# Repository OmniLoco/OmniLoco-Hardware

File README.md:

OmniLoco Hardware
=================

The official repository for all of the hardware used by and created for the OmniLoco
project.

Repository Contents
-------------------

### Top Level

* OmniRotor -- Sources for the OmniRotor platform, a sophisticated autonomous aircraft controller.
* Library -- Script files for individual EAGLE packages, symbols and devices. See below for more
information.

### Tools

* OmniRotor_PogoPlate -- Used for the automated programming and testing of production OmniRotor devices.

EAGLE Library
-------------
The EAGLE library used for the OmniLoco project has been split up into individual package,
symbol and device script files. This is done so git can track the changes of each individual
part of the library, rather than simply tracking one monolithic binary file.

Exporting the library must be done before every commit which which includes changes to the
library. This process could be automated, although it's much easier to do it by hand for now.

### Building the library from this repo
1. Open a new library (or open an existing OmniLoco library)
2. Run the lbrbuild.ulp script (located in the `Library` directory)
3. Point to the generated (or downloaded from git) `librarydefaults.scr` when prompted
4. All the packages/devices/symbols are added to the new/existing library

### Exporting the library after making changes
If you are on Windows and using EAGLE 6.3.0 you can use the `Library/_dump_library.bat` script

1. Open the OmniLoco library
2. File > Export > Script (This will generate one large script with all the devices in it)
3. Save it to the `Library` directory as `_full_library.scr`
4. Run the lbrdump.ulp script (located in the `Library` directory)
5. Open the exported library file (`_full_library.scr` from step 3)

The method for exporting and building an EAGLE library using script files is adapted from 
[DangerousPrototypes][1].

Contributing
------------

1. Fork it.
2. Create a branch (`git checkout -b my_hardware`)
3. Commit your changes (`git commit -am "Added Awesome Changes"`)
4. Push to the branch (`git push origin my_hardware`)
5. Create an issue with a link to your branch, or submit a pull request
6. Enjoy a refreshing beverage and wait

License
-------
All OmniLoco hardware is open source and compliant with the [Open Source Hardware Definition][2].

Copyright (c) 2012 by the OmniLoco Foundation. This work is made available under the terms of the Creative Commons Attribution-ShareAlike 3.0 license, http://creativecommons.org/licenses/by-sa/3.0/.

[1]: http://dangerousprototypes.com/docs/Dangerous_Prototypes_Cadsoft_Eagle_parts_library
[2]: http://freedomdefined.org/OSHW#Open_Source_Hardware_.28OSHW.29_Definition_1.0

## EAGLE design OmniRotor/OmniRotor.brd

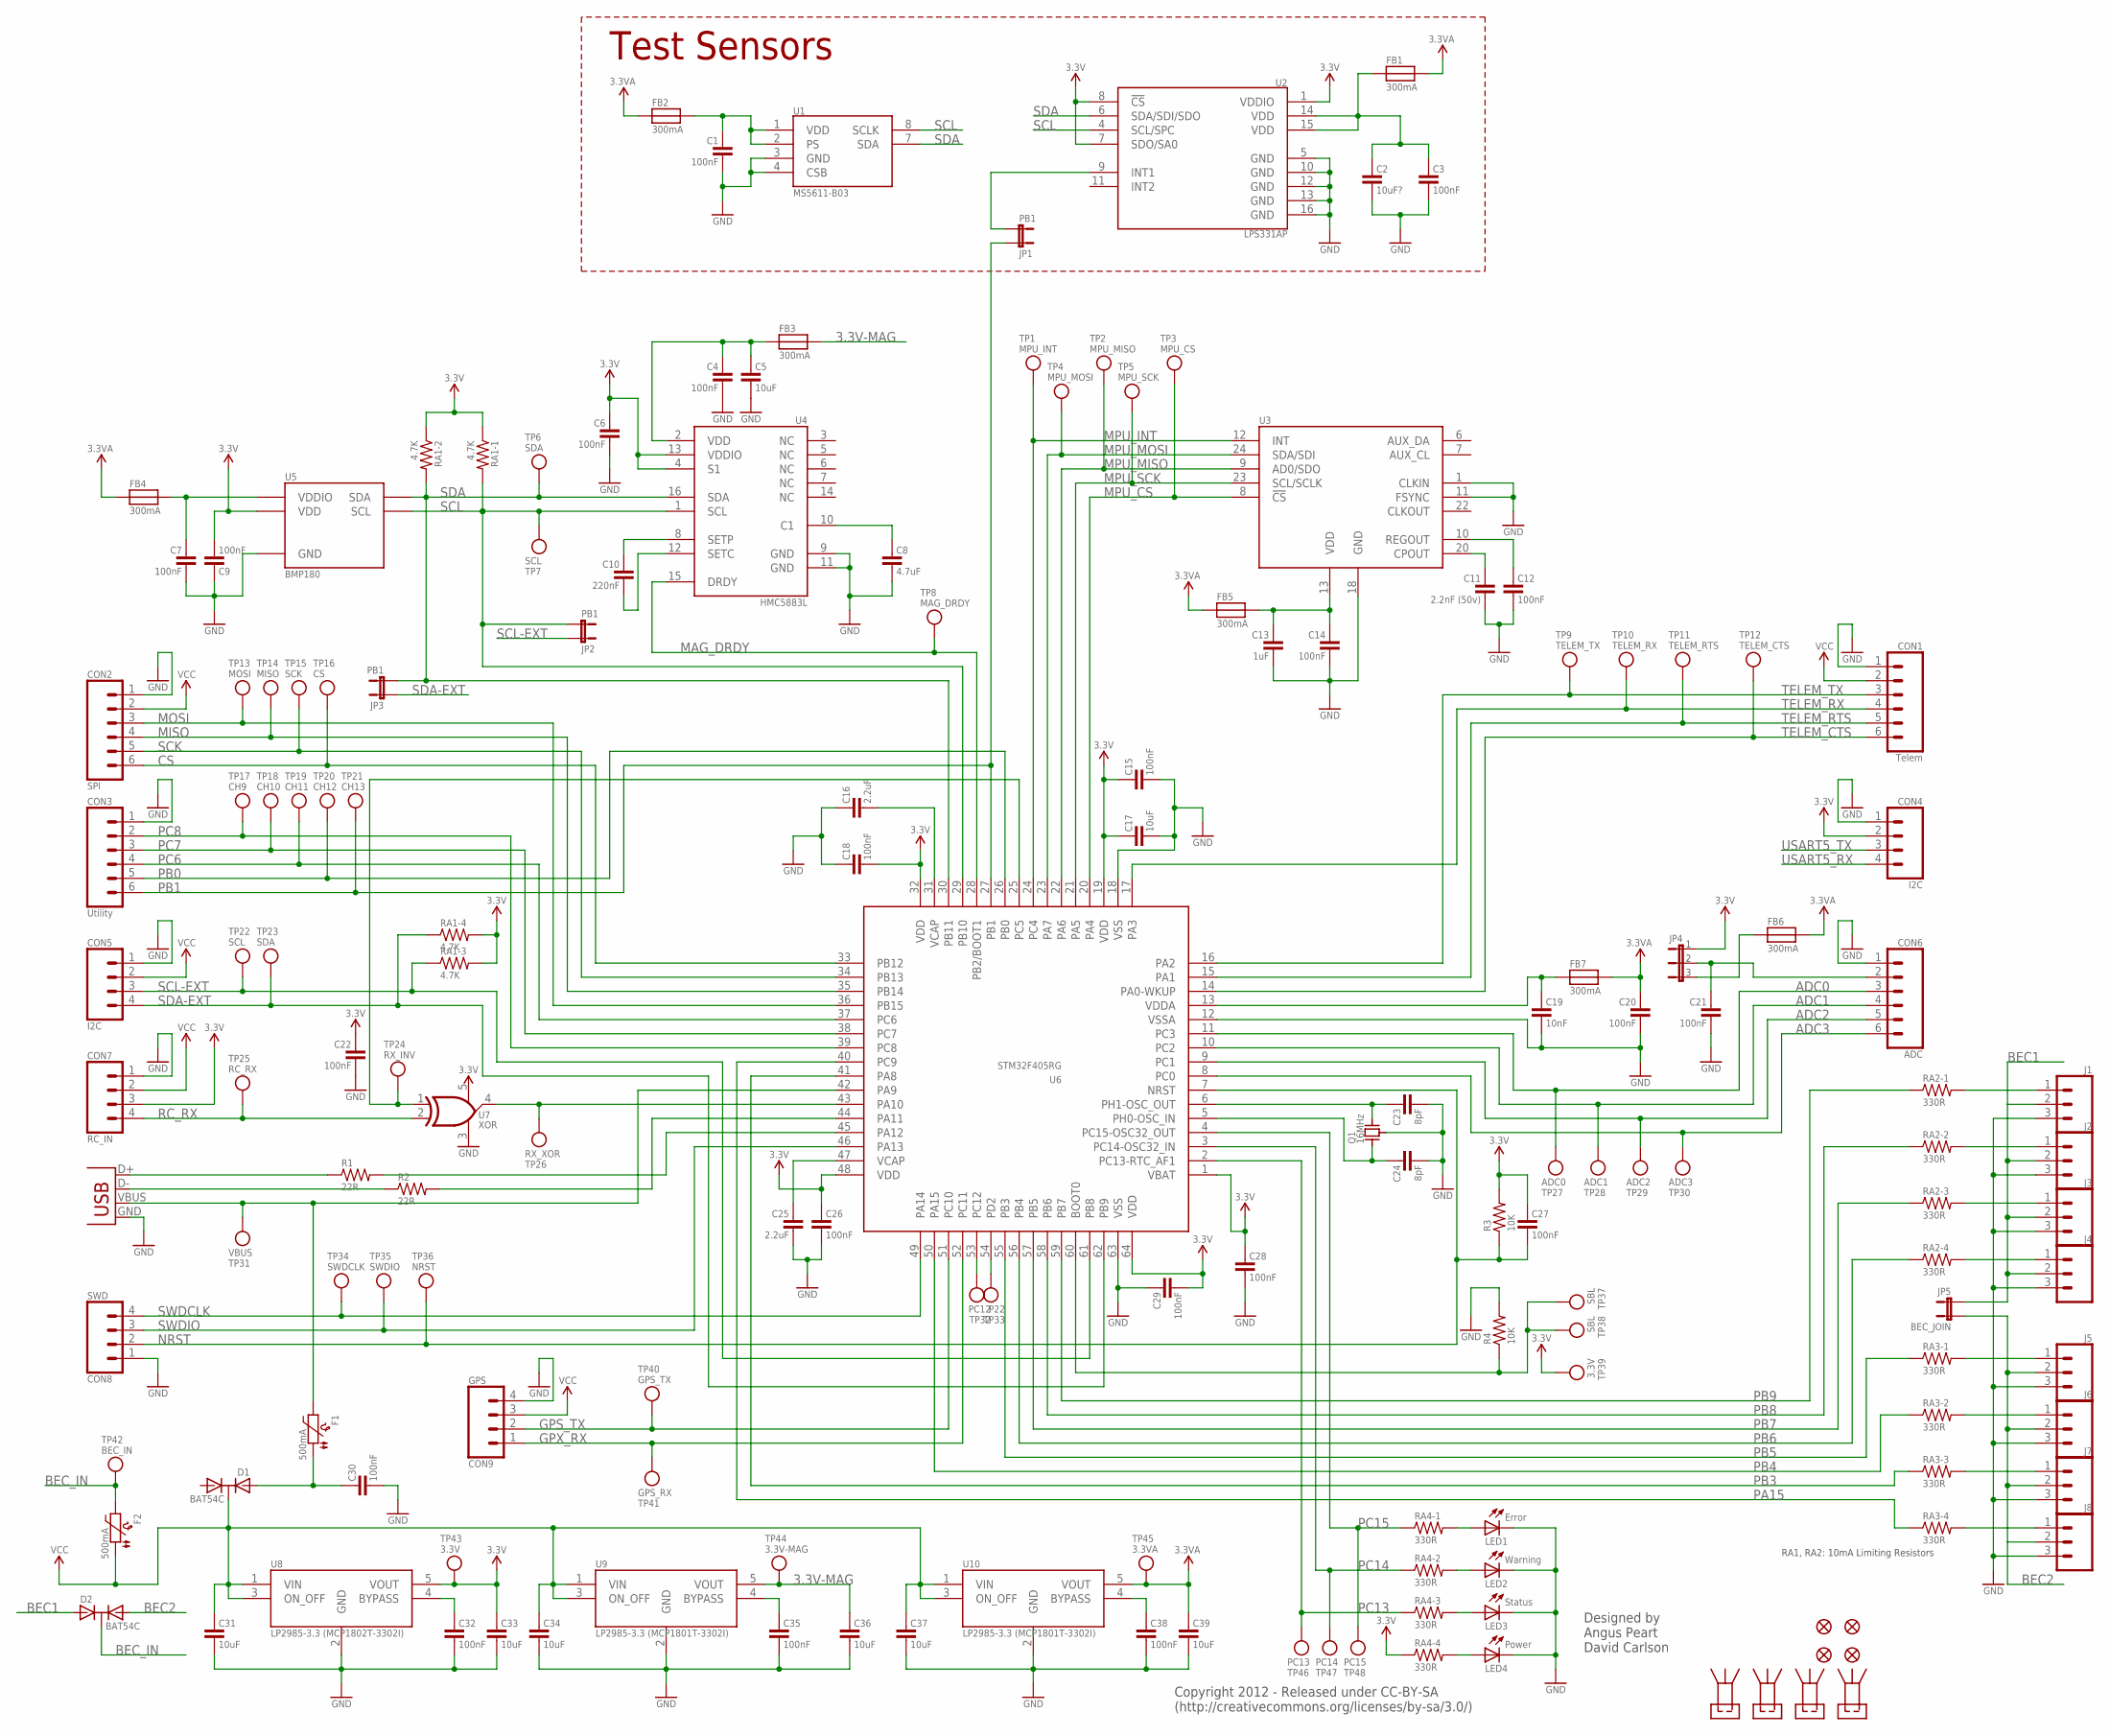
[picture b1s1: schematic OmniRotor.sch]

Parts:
C1, C3, C4, C6, C7, C9, C12, C14, C15, C18, C20, C21, C22, C26, C27, C28, C29, C30, C32, C35, C38: 100nF; 0402-CAP@1
C2: 10uF?; 0603@1
C5: 10uF; 0805@1
C8: 4.7uF; 0603@1
C10: 220nF; 0402-CAP@1
C11: 2.2nF (50v); 0402-CAP@1
C13: 1uF; 0603@1
C16, C25: 2.2uF; 0603@1
C17, C31, C33, C34, C36, C37, C39: 10uF; 0805
C19: 10nF; 0402-CAP@1
C23, C24: 8pF; 0402-CAP@1
CON1: Telem; SM06B-SRSS-TB
CON2: SPI; SM06B-SRSS-TB
CON3: Utility; SM06B-SRSS-TB
CON4, CON5: I2C; SM04B-SRSS-TB
CON6: ADC; SM06B-SRSS-TB
CON7: RC_IN; SM04B-SRSS-TB
CON8: SWD; BM04B-SRSS-TB
CON9: GPS; SM04B-SRSS-TB
D1, D2: BAT54C; SOT23
F1, F2: 500mA; 1210-PTC
FB1, FB2, FB3, FB4, FB5, FB6, FB7: 300mA; 0603
FID1, FID2, FID3, FID4: FIDUCIAL1X2.5; FIDUCIAL-1X2.5
J1, J2, J3, J4, J5, J6, J7, J8: M03PTH; 1X03
JP1, JP2, JP3: PB1; SJ_2_NO
JP4: JUMPER-31-2; SJ_3_PASTE1&2
JP5: BEC_JOIN; SJ_2_NO
LED1: Error; 0603_LED
LED2: Warning; 0603_LED
LED3: Status; 0603_LED
LED4: Power; 0603_LED
LP1, LP2, LP3, LP4: LIGHTPIPE; VLP-LIGHTPIPES
Q1: 16MHz; CRYSTAL_3-2X2-5
R1, R2: 22R; 0402-RES
R3, R4: 10K; 0402-RES
RA1: 4.7K; 1206-ARRAY
RA2, RA3, RA4: 330R; 1206-ARRAY
TP1: MPU_INT; TESTPOINT_ROUND_0.7MM
TP2: MPU_MISO; TESTPOINT_ROUND_0.7MM
TP3: MPU_CS; TESTPOINT_ROUND_0.7MM
TP4: MPU_MOSI; TESTPOINT_ROUND_0.7MM
TP5: MPU_SCK; TESTPOINT_ROUND_0.7MM
TP6, TP23: SDA; TESTPOINT_ROUND_0.7MM
TP7, TP22: SCL; TESTPOINT_ROUND_0.7MM
TP8: MAG_DRDY; TESTPOINT_ROUND_0.7MM
TP9: TELEM_TX; TESTPOINT_ROUND_0.7MM
TP10: TELEM_RX; TESTPOINT_ROUND_0.7MM
TP11: TELEM_RTS; TESTPOINT_ROUND_0.7MM
TP12: TELEM_CTS; TESTPOINT_ROUND_0.7MM
TP13: MOSI; TESTPOINT_ROUND_0.7MM
TP14: MISO; TESTPOINT_ROUND_0.7MM
TP15: SCK; TESTPOINT_ROUND_0.7MM
TP16: CS; TESTPOINT_ROUND_0.7MM
TP17: CH9; TESTPOINT_ROUND_0.7MM
TP18: CH10; TESTPOINT_ROUND_0.7MM
TP19: CH11; TESTPOINT_ROUND_0.7MM
TP20: CH12; TESTPOINT_ROUND_0.7MM
TP21: CH13; TESTPOINT_ROUND_0.7MM
TP24: RX_INV; TESTPOINT_ROUND_0.7MM
TP25: RC_RX; TESTPOINT_ROUND_0.7MM
TP26: RX_XOR; TESTPOINT_ROUND_0.7MM
TP27: ADC0; TESTPOINT_ROUND_0.7MM
TP28: ADC1; TESTPOINT_ROUND_0.7MM
TP29: ADC2; TESTPOINT_ROUND_0.7MM
TP30: ADC3; TESTPOINT_ROUND_0.7MM
TP31: VBUS; TESTPOINT_ROUND_0.7MM
TP32: PC12; TESTPOINT_ROUND_0.7MM
TP33: P22; TESTPOINT_ROUND_0.7MM
TP34: SWDCLK; TESTPOINT_ROUND_0.7MM
TP35: SWDIO; TESTPOINT_ROUND_0.7MM
TP36: NRST; TESTPOINT_ROUND_0.7MM
TP37: SBL; TESTPOINT_ROUND_1MM
TP38: SBL; TESTPOINT_ROUND_1.5MM
TP39: 3.3V; TESTPOINT_ROUND_1.5MM
TP40: GPS_TX; TESTPOINT_ROUND_0.7MM
TP41: GPS_RX; TESTPOINT_ROUND_0.7MM
TP42: BEC_IN; TESTPOINT_ROUND_0.7MM
TP43: 3.3V; TESTPOINT_ROUND_0.7MM
TP44: 3.3V-MAG; TESTPOINT_ROUND_0.7MM
TP45: 3.3VA; TESTPOINT_ROUND_0.7MM
TP46: PC13; TESTPOINT_ROUND_0.7MM
TP47: PC14; TESTPOINT_ROUND_0.7MM
TP48: PC15; TESTPOINT_ROUND_0.7MM
U1: MS5611-B03; MS5611
U2: LPS331AP; HCLGA-16L
U3: MPU6000; QFN-24
U4: HMC5883L; 16LPCC
U5: BMP180
U6: STM32F405RG; LQFP64
U7: XOR; SC-70-5
U8: LP2985-3.3 (MCP1802T-3302I); SOT-23-5
U9, U10: LP2985-3.3 (MCP1801T-3302I); SOT-23-5
USB1: USB-MICRO-B

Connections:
3.3V: C6.1, C9.2, C15.1, C17.1, C18.2, C22.1, C26.1, C27.1, C28.1, C29.2, C33.1, CON4.2, CON7.3, JP4.1, R3.2, RA1.A1 (1), RA1.B1 (1), RA1.C2 (2), RA1.D2 (2), RA4.D1 (1), TP39.1, TP43.1, U2.1 (VDDIO), U2.7 (SDO/SA0), U2.8 (!CS), U4.4 (S1), U4.13 (VDDIO), U5.2 (VDD), U6.1 (VBAT), U6.19 (VDD), U6.32 (VDD), U6.48 (VDD), U6.64 (VDD), U7.5 (VCC), U8.5 (VOUT)
3.3V-MAG: C36.1, FB3.2, TP44.1, U9.5 (VOUT)
3.3VA: C20.1, C39.1, FB1.2, FB2.1, FB4.1, FB5.1, FB6.2, FB7.2, TP45.1, U10.5 (VOUT)
ADC0: CON6.3, TP27.1, U6.11 (PC3)
ADC1: CON6.4, TP28.1, U6.10 (PC2)
ADC2: CON6.5, TP29.1, U6.9 (PC1)
ADC3: CON6.6, TP30.1, U6.8 (PC0)
BEC1: D2.1, J1.2, J2.2, J3.2, J4.2, JP5.1
BEC2: D2.2, J5.2, J6.2, J7.2, J8.2, JP5.2
BEC_IN: D2.3, F2.1, TP42.1
CS: CON2.6, TP16.1, U6.33 (PB12)
GND: C1.2, C2.2, C3.2, C4.2, C5.2, C6.2, C7.2, C8.2, C9.1, C11.2, C12.2, C13.2, C14.2, C15.2, C16.1, C17.2, C18.1, C19.2, C20.2, C21.2, C22.2, C23.2, C24.2, C25.2, C26.2, C28.2, C29.1, C30.2, C31.2, C32.2, C33.2, C34.2, C35.2, C36.2, C37.2, C38.2, C39.2, CON1.1, CON2.1, CON3.1, CON4.1, CON5.1, CON6.1, CON7.1, CON8.1, CON9.4, J1.3, J2.3, J3.3, J4.3, J5.3, J6.3, J7.3, J8.3, LED1.2 (C), LED2.2 (C), LED3.2 (C), LED4.2 (C), Q1.2 (GND), Q1.4 (GND), R4.2, U1.3 (GND), U1.4 (CSB), U2.5 (GND), U2.10 (GND), U2.12 (GND), U2.13 (GND), U2.16 (GND), U3.1 (CLKIN), U3.11 (FSYNC), U3.18 (GND), U4.9 (GND), U4.11 (GND), U5.7 (GND), U6.12 (VSSA), U6.18 (VSS), U6.63 (VSS), U7.3 (GND), U8.2 (GND), U9.2 (GND), U10.2 (GND), USB1.GND
GPS_TX: CON9.2, TP40.1, U6.51 (PC10)
GPX_RX: CON9.1, TP41.1, U6.52 (PC11)
MAG_DRDY: TP8.1, U4.15 (DRDY), U6.28 (PB2/BOOT1)
MISO: CON2.4, TP14.1, U6.35 (PB14)
MOSI: CON2.3, TP13.1, U6.36 (PB15)
MPU_CS: TP3.1, U3.8 (!CS!), U6.20 (PA4)
MPU_INT: TP1.1, U3.12 (INT), U6.24 (PC4)
MPU_MISO: TP2.1, U3.9 (AD0/SDO), U6.22 (PA6)
MPU_MOSI: TP4.1, U3.24 (SDA/SDI), U6.23 (PA7)
MPU_SCK: TP5.1, U3.23 (SCL/SCLK), U6.21 (PA5)
unnamed: C19.1, FB7.1, U6.13 (VDDA)
unnamed: C23.1, Q1.3 (2), U6.6 (PH1-OSC_OUT)
unnamed: C24.1, Q1.1, U6.5 (PH0-OSC_IN)
unnamed: C30.1, D1.1, F1.2
unnamed: C32.1, U8.4 (BYPASS)
unnamed: TP24.1, U6.25 (PC5), U7.1 (I0)
unnamed: C35.1, U9.4 (BYPASS)
unnamed: R1.1, USB1.D+
unnamed: R2.1, USB1.D-
unnamed: R2.2, U6.44 (PA11)
unnamed: R1.2, U6.45 (PA12)
unnamed: TP26.1, U6.43 (PA10), U7.4 (O)
unnamed: C10.1, U4.8 (SETP)
unnamed: C10.2, U4.12 (SETC)
unnamed: C13.1, C14.1, FB5.2, U3.13 (VDD)
unnamed: C8.1, U4.10 (C1)
unnamed: C21.1, CON6.2, JP4.2
unnamed: C2.1, C3.1, FB1.1, U2.14 (VDD), U2.15 (VDD)
unnamed: LED4.1 (A), RA4.D2 (2)
unnamed: LED3.1 (A), RA4.C2 (2)
unnamed: FB6.1, JP4.3
unnamed: LED2.1 (A), RA4.B2 (2)
unnamed: C11.1, U3.20 (CPOUT)
unnamed: C12.1, U3.10 (REGOUT)
unnamed: LED1.1 (A), RA4.A2 (2)
unnamed: J2.1, RA2.B2 (2)
unnamed: J3.1, RA2.C2 (2)
unnamed: J4.1, RA2.D2 (2)
unnamed: J1.1, RA2.A2 (2)
unnamed: J6.1, RA3.B2 (2)
unnamed: J7.1, RA3.C2 (2)
unnamed: J8.1, RA3.D2 (2)
unnamed: J5.1, RA3.A2 (2)
unnamed: JP1.2, U2.9 (INT1)
unnamed: R4.1, TP37.1, TP38.1, U6.60 (BOOT0)
unnamed: C38.1, U10.4 (BYPASS)
unnamed: C4.1, C5.1, FB3.1, U4.2 (VDD)
unnamed: C7.1, FB4.2, U5.3 (VDDIO)
unnamed: C1.1, FB2.2, U1.1 (VDD), U1.2 (PS)
NRST: C27.2, CON8.2, R3.1, TP36.1, U6.7 (NRST)
PA15: RA3.D1 (1), U6.40 (PC9)
PB0: CON3.5, TP20.1, U6.26 (PB0)
PB1: CON3.6, JP1.1, TP21.1, U6.27 (PB1)
PB3: RA3.C1 (1), U6.41 (PA8)
PB4: RA3.B1 (1), U6.50 (PA15)
PB5: RA3.A1 (1), U6.55 (PB3)
PB6: RA2.D1 (1), U6.56 (PB4)
PB7: RA2.C1 (1), U6.57 (PB5)
PB8: RA2.B1 (1), U6.58 (PB6)
PB9: RA2.A1 (1), U6.59 (PB7)
PC6: CON3.4, TP19.1, U6.37 (PC6)
PC7: CON3.3, TP18.1, U6.38 (PC7)
PC8: CON3.2, TP17.1, U6.39 (PC8)
PC13: RA4.C1 (1), TP46.1, U6.2 (PC13-RTC_AF1)
PC14: RA4.B1 (1), TP47.1, U6.3 (PC14-OSC32_IN)
PC15: RA4.A1 (1), TP48.1, U6.4 (PC15-OSC32_OUT)
RC_RX: CON7.4, TP25.1, U7.2 (I1)
SCK: CON2.5, TP15.1, U6.34 (PB13)
SCL: JP2.2, RA1.A2 (2), TP7.1, U1.8 (SCLK), U2.4 (SCL/SPC), U4.1 (SCL), U5.5 (SCL), U6.29 (PB10)
SCL-EXT: CON5.3, JP2.1, RA1.C1 (1), TP22.1, U6.61 (PB8)
SDA: JP3.2, RA1.B2 (2), TP6.1, U1.7 (SDA), U2.6 (SDA/SDI/SDO), U4.16 (SDA), U5.6 (SDA), U6.30 (PB11)
SDA-EXT: CON5.4, JP3.1, RA1.D1 (1), TP23.1, U6.62 (PB9)
SWDCLK: CON8.4, TP34.1, U6.49 (PA14)
SWDIO: CON8.3, TP35.1, U6.46 (PA13)
TELEM_CTS: CON1.6, TP12.1, U6.14 (PA0-WKUP)
TELEM_RTS: CON1.5, TP11.1, U6.15 (PA1)
TELEM_RX: CON1.4, TP10.1, U6.17 (PA3)
TELEM_TX: CON1.3, TP9.1, U6.16 (PA2)
USART5_RX: CON4.4, TP33.1, U6.54 (PD2)
USART5_TX: CON4.3, TP32.1, U6.53 (PC12)
VCAP@1: C16.2, U6.31 (VCAP)
VCAP@2: C25.1, U6.47 (VCAP)
VCC: C31.1, C34.1, C37.1, CON1.2, CON2.2, CON5.2, CON7.2, CON9.3, D1.3, F2.2, U8.1 (VIN), U8.3 (ON_OFF), U9.1 (VIN), U9.3 (ON_OFF), U10.1 (VIN), U10.3 (ON_OFF)
VUSB: F1.1, TP31.1, U6.42 (PA9), USB1.VBUS

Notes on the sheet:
RA1, RA2: 10mA Limiting Resistors
Test Sensors
Designed by Angus Peart David Carlson
Copyright 2012 - Released under CC-BY-SA (http://creativecommons.org/licenses/by-sa/3.0/)

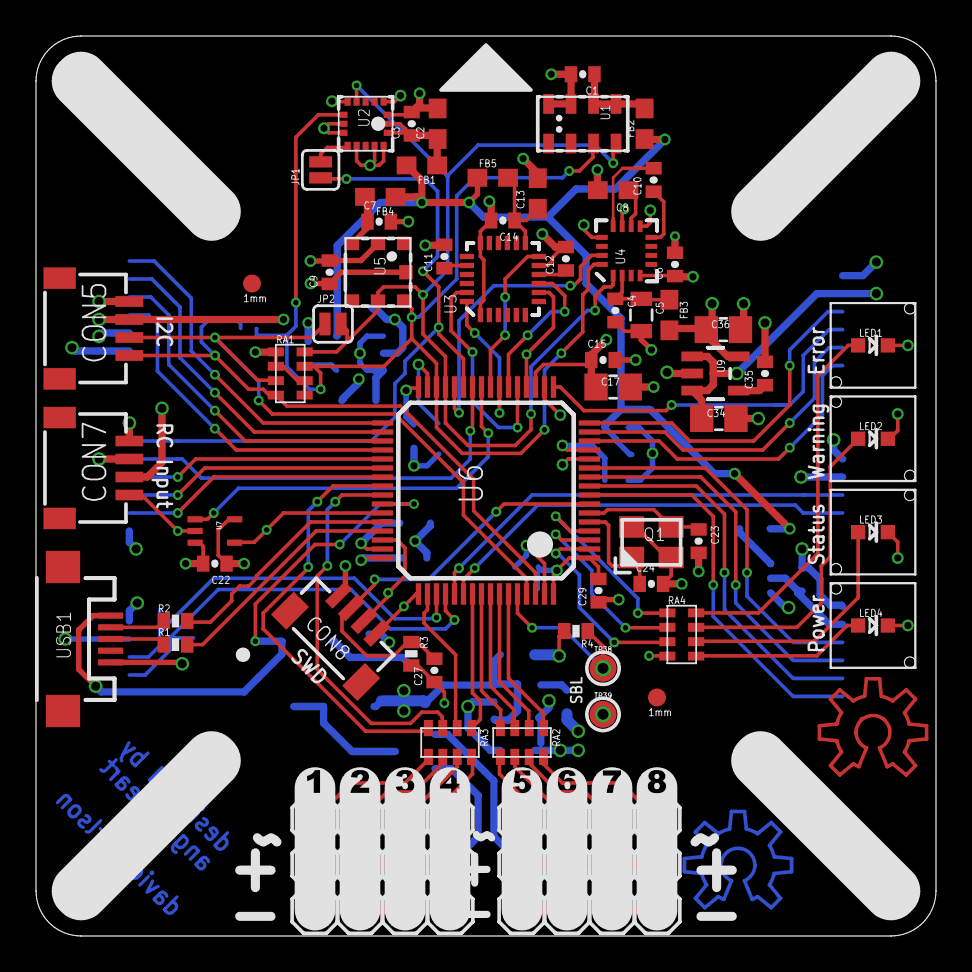
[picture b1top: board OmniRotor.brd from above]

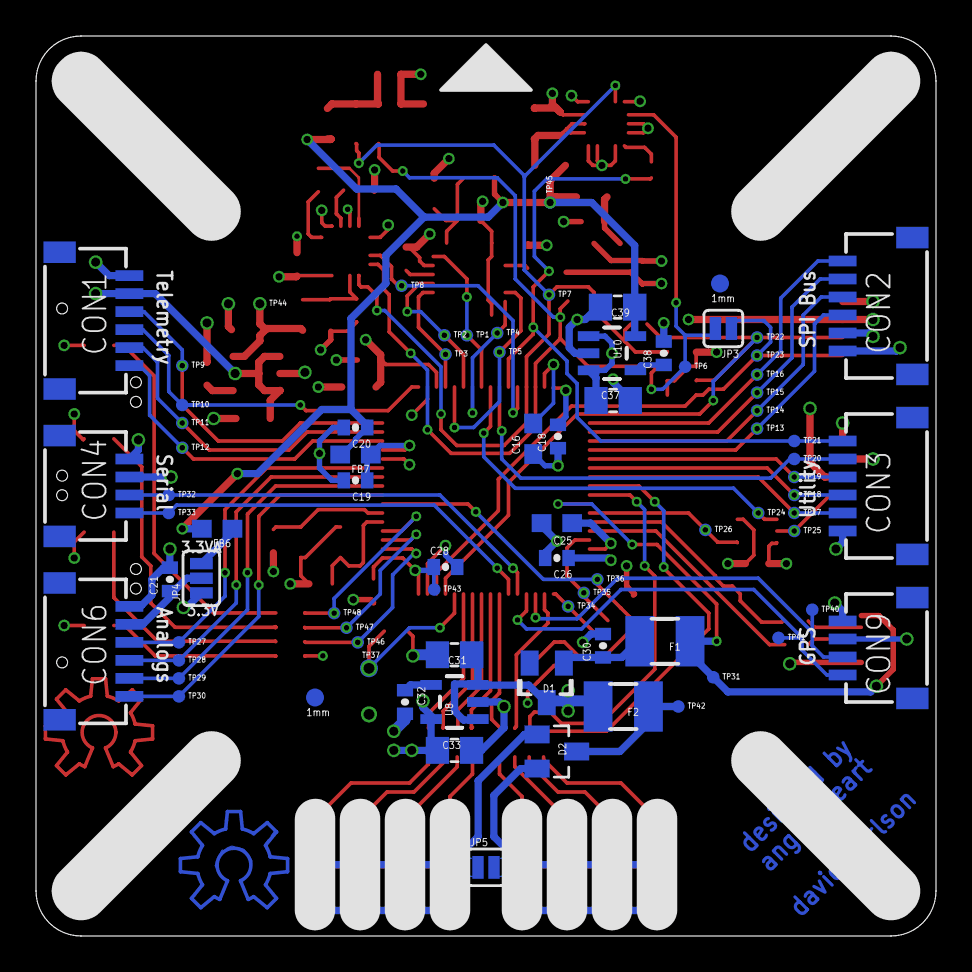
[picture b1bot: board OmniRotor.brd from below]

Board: 4 copper layers, 50.0 x 50.0 mm, 160 parts (80 on the bottom side), 96 nets.

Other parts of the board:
U$16: SILK-SERVO-1
U$24: SILK-SERVO-4
U$28: SILK-SERVO-3
U$31: SILK-SERVO-2
U$32: SILK-SERVO-5
U$33: SILK-SERVO-6
U$34: SILK-SERVO-7
U$35: SILK-SERVO-8

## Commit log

2011-10-15 Initial Commit. Added OmniRotor v1.0
2011-10-15 Removed invalid gerbers.
2011-10-15 Changes pressure sensor from BMP085 to newer BMP180. Minor silkscreen updates and added .gitignore file.
2011-10-15 Changes pressure sensor from BMP085 to newer BMP180. Minor silkscreen updates.
2011-10-30 Fixed LED names on schematic. Added bCream gerbers.
2011-10-30 Added testpoints for pogopin programming.
2011-10-30 Added OmnoRotor_PogoPlate design, used in a production programming and testing tool.
2011-10-30 Added TELEM_USART testpoints.
2011-10-30 Added markdown formatted readme file.
2011-10-30 Added mechanical vision alignment fiducials.
2011-10-30 Added EAGLE Library files and cleaned up schematic somewhat.
2011-10-30 Added license to README and added a description to the EAGLE library.
2011-11-10 Complete library update and cleanup.
2011-11-10 Updated Schematic/Board files to reflect changes in library. Note that some parts (such as STM32/CAPACITOR) use old definitions because of rename.
2011-11-10 Updated 10uF Capacitors from 0603 to 0805 packages.
2011-11-10 Switched crystal from 8MHz to 12MHz version.
2011-11-10 Renamed schematic and board files by removing versioning. Git tags will now be used for versioning.
2011-11-16 Added redundant BEC supply circuit. Added ADC connector voltage jumper with filtering. Components: Added; FB2, C34, C35, D2, C36; Removed; C27.
2011-11-16 Updated jumper symbol.
2011-11-16 Changed LED to light-pipe footprints.
2011-11-16 Updated OR pogoplate to reflect OR changes.
2011-11-16 Initial OM commit.
2011-11-18 Added solder jumper to bridge BEC inputs for single BEC systems. Removed: C25, C36.
2012-12-01 Q4 2012 Changes
    - Updated MPU3000 to MPU6000
    - Removed Accelerometer
    - Removed EEPROM
    - Added MAG3110 and LPS331AP (for testing and verification)
    - Updated silkscreen
    - Fixed some routing and internal ground planes
2012-12-01 Renamed EAGLE files, removed version from filename.
2012-12-06 Changed debug interface from JTAG to SWD.
    Frees up 2 GPIO. Also added pull-up and decoupling cap to reset line.
2012-12-11 More updates for Q4 2012 production.
    - Added MS5611 pressure sensor
    - Removed MAG3110
    - Remapped some I/O pins
    - Added additional UART connector
    - Added Utility connector (PWM+ADC+SPI)
    - Cleaned up all routing
2012-12-11 Fixed automated library dump
    Automated library dump is working on EAGLE-6.0.3 on Windows.
2012-12-15 Board functional design done, silkscreen updated
    - Board routing and pin re-mapping complete
    - Started on silkscreen changes
2012-12-16 Silkscreen and component footprint updates
